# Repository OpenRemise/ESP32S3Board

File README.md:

# ESP32S3Board

<a href="https://openremise.at">
<picture>
  <source media="(prefers-color-scheme: dark)" srcset="https://github.com/OpenRemise/.github/raw/master/data/icons/icon_dark.svg">
  
</picture>
</a>

The EPS32S3Board was a prototype of a board with ESP32-S3 processor in [Arduino](https://www.arduino.cc/) form factor. Due to the inadequacies of the stackable headers, Arduino compatibility was abandoned and single-board solutions are now used.

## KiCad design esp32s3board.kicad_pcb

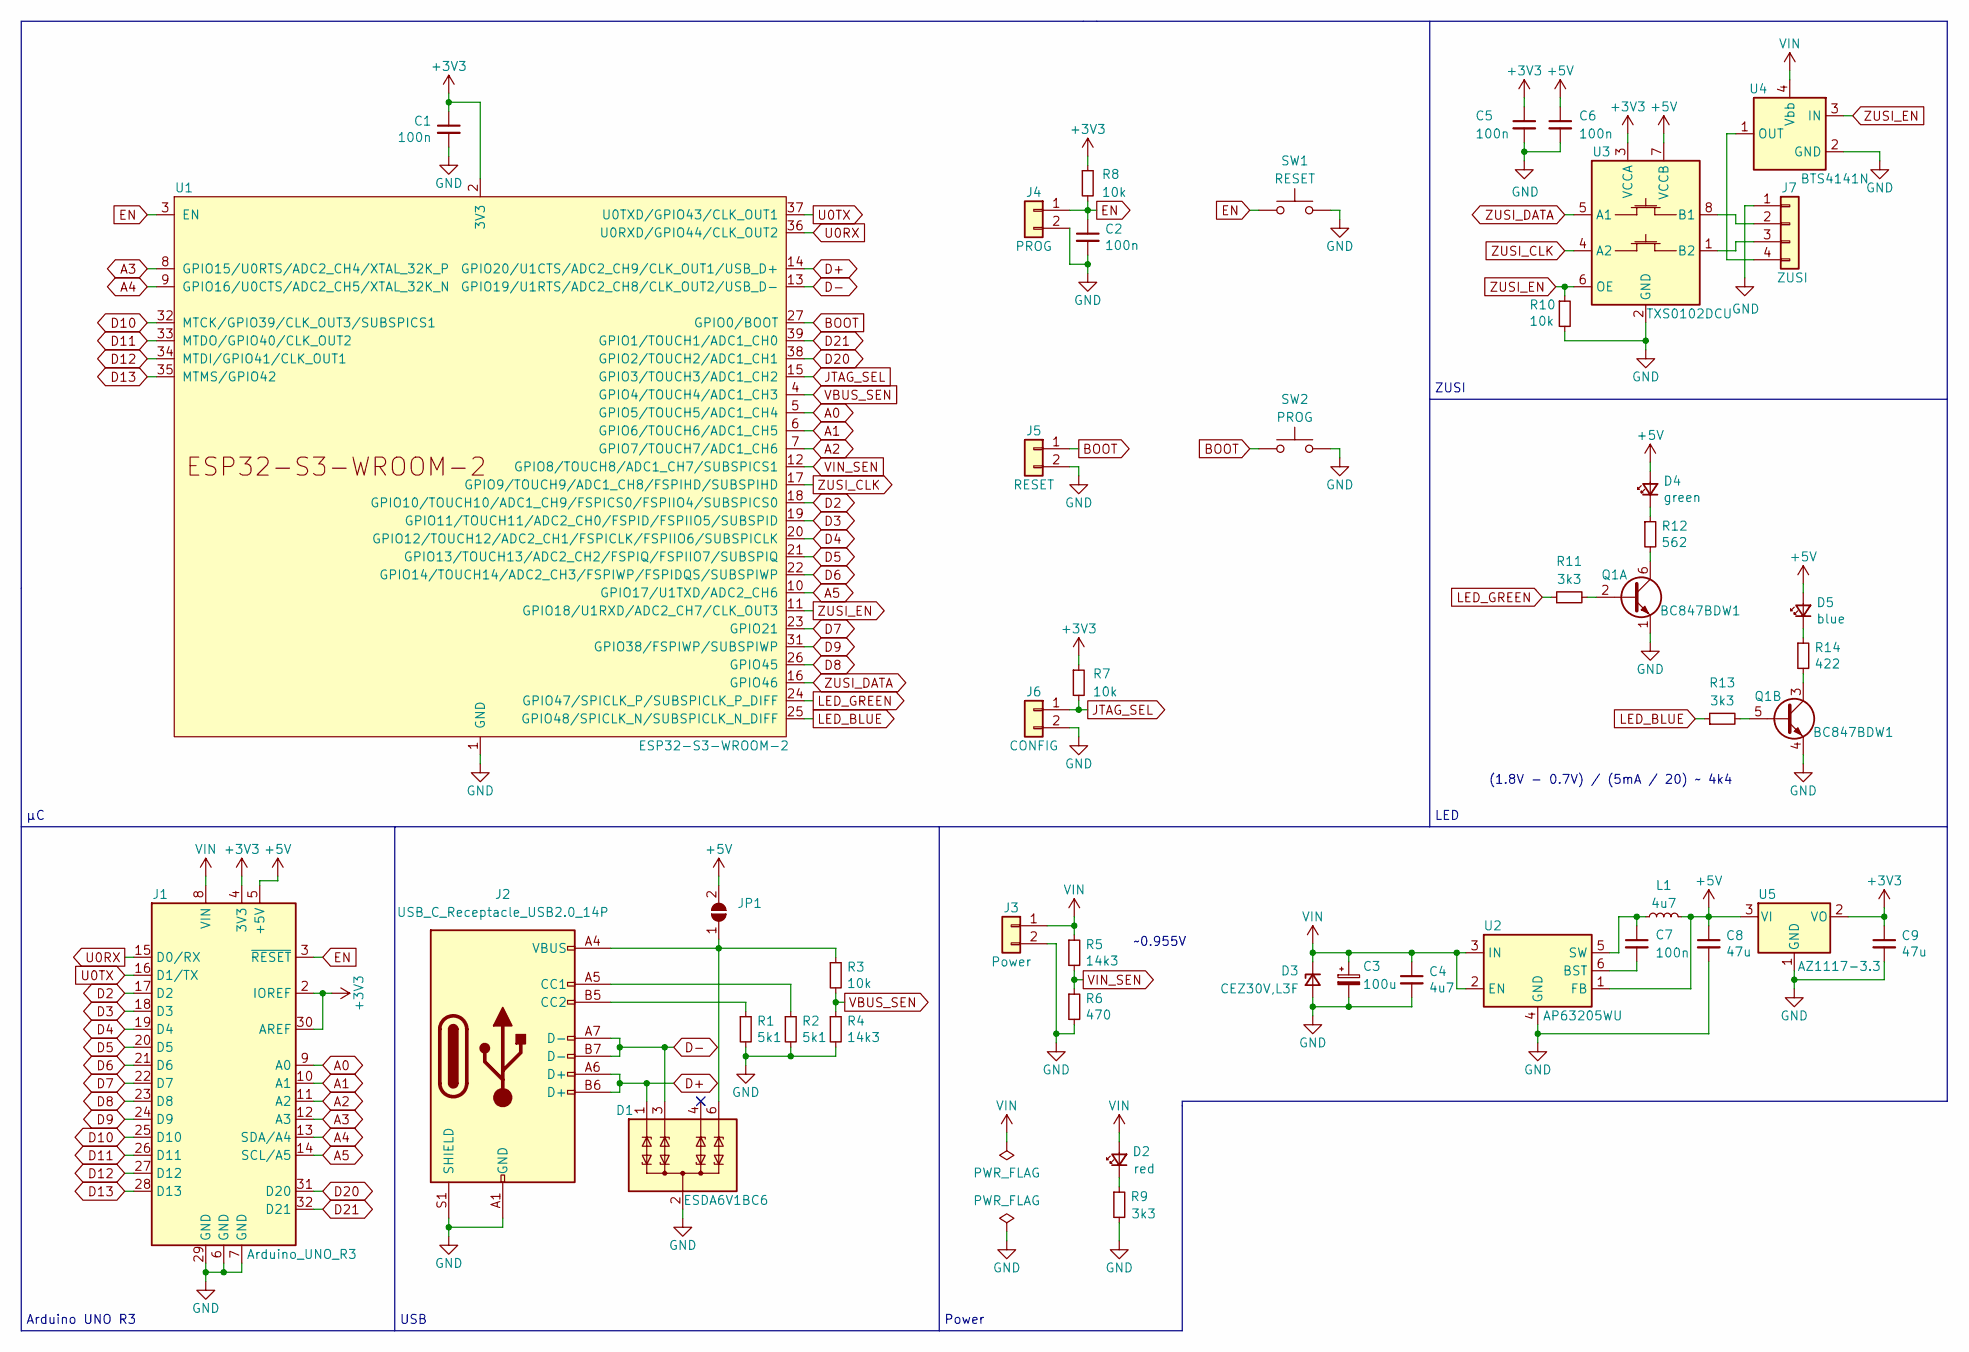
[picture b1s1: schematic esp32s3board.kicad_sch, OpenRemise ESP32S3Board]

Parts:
C1, C2, C5, C6, C7: 100n; C_0402_1005Metric
C3: 100u; CP_Elec_6.3x7.7
C4: 4u7; C_1206_3216Metric
C8, C9: 47u; C_1206_3216Metric
D1: ESDA6V1BC6; SOT-23-6
D2: red; D_0402_1005Metric
D3: CEZ30V,L3F; D_SOD-523
D4: green; D_0402_1005Metric
D5: blue; D_0402_1005Metric
J1: Arduino_UNO_R3; Arduino_UNO_R3_WithMountingHoles
J2: USB_C_Receptacle_USB2.0_14P; USB_C_Receptacle_GCT_USB4105-xx-A_16P_TopMnt_Horizontal
J3: Power; PinHeader_1x02_P2.54mm_Horizontal
J4: PROG; PinHeader_1x02_P2.54mm_Horizontal
J5: RESET; PinHeader_1x02_P2.54mm_Horizontal
J6: CONFIG; PinHeader_1x02_P2.54mm_Horizontal
J7: ZUSI; JST_SH_SM04B-SRSS-TB_1x04-1MP_P1.00mm_Horizontal
JP1: SolderJumper_2_Open; SolderJumper-2_P1.3mm_Open_Pad1.0x1.5mm
L1: 4u7; L_0805_2012Metric
Q1: BC847BDW1; SOT-363_SC-70-6
R1, R2: 5k1; R_0402_1005Metric
R3, R7, R8, R10: 10k; R_0402_1005Metric
R4, R5: 14k3; R_0402_1005Metric
R6: 470; R_0402_1005Metric
R9, R11, R13: 3k3; R_0402_1005Metric
R12: 562; R_0402_1005Metric
R14: 422; R_0402_1005Metric
SW1: RESET; SW_SPST_EVPBF
SW2: PROG; SW_SPST_EVPBF
U1: ESP32-S3-WROOM-2
U2: AP63205WU; TSOT-23-6
U3: TXS0102DCU; VSSOP-8_2.3x2mm_P0.5mm
U4: BTS4141N; SOT-223
U5: AZ1117-3.3; SOT-89-3

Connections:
+3V3: C1.1, C5.1, C9.1, J1.2 (IOREF), J1.4 (3V3), J1.30 (AREF), R7.1, R8.1, U1.2 (3V3), U3.3 (VCCA), U5.2 (VO)
+5V: C6.1, C8.1, D4.2 (A), D5.2 (A), J1.5 (+5V), JP1.2 (B), L1.2, U2.1 (FB), U3.7 (VCCB), U5.3 (VI)
A0: J1.9 (A0), U1.5 (GPIO5/TOUCH5/ADC1_CH4)
A1: J1.10 (A1), U1.6 (GPIO6/TOUCH6/ADC1_CH5)
A2: J1.11 (A2), U1.7 (GPIO7/TOUCH7/ADC1_CH6)
A3: J1.12 (A3), U1.8 (GPIO15/U0RTS/ADC2_CH4/XTAL_32K_P)
A4: J1.13 (SDA/A4), U1.9 (GPIO16/U0CTS/ADC2_CH5/XTAL_32K_N)
A5: J1.14 (SCL/A5), U1.10 (GPIO17/U1TXD/ADC2_CH6)
BOOT: J5.1, SW2.1, U1.27 (GPIO0/BOOT)
D2: J1.17 (D2), U1.18 (GPIO10/TOUCH10/ADC1_CH9/FSPICS0/FSPIIO4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)
D3: J1.18 (D3), U1.19 (GPIO11/TOUCH11/ADC2_CH0/FSPID/FSPIIO5/S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)
D4: J1.19 (D4), U1.20 (GPIO12/TOUCH12/ADC2_CH1/FSPICLK/FSPIIO6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)
D5: J1.20 (D5), U1.21 (GPIO13/TOUCH13/ADC2_CH2/FSPIQ/FSPIIO7/S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)
D6: J1.21 (D6), U1.22 (GPIO14/TOUCH14/ADC2_CH3/FSPIWP/FSPIDQS/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)
D7: J1.22 (D7), U1.23 (GPIO21)
D8: J1.23 (D8), U1.26 (GPIO45)
D9: J1.24 (D9), U1.31 (GPIO38/FSPIWP/SUBSPIWP)
D10: J1.25 (D10), U1.32 (MTCK/GPIO39/CLK_OUT3/SUBSPICS1)
D11: J1.26 (D11), U1.33 (MTDO/GPIO40/CLK_OUT2)
D12: J1.27 (D12), U1.34 (MTDI/GPIO41/CLK_OUT1)
D13: J1.28 (D13), U1.35 (MTMS/GPIO42)
D20: J1.31 (D20), U1.38 (GPIO2/TOUCH2/ADC1_CH1)
D21: J1.32 (D21), U1.39 (GPIO1/TOUCH1/ADC1_CH0)
D+: D1.1 (TVS1), J2.A6 (D+), J2.B6 (D+), U1.14 (GPIO20/U1CTS/ADC2_CH9/CLK_OUT1/USB_D+)
D-: D1.3 (TVS2), J2.A7 (D-), J2.B7 (D-), U1.13 (GPIO19/U1RTS/ADC2_CH8/CLK_OUT2/USB_D-)
EN: C2.1, J1.3 (~RESET), J4.1, R8.2, SW1.1, U1.3 (EN)
GND: C1.2, C2.2, C3.2, C4.2, C5.2, C6.2, C8.2, C9.2, D1.2 (COM), D1.5 (COM), D3.2 (A), J1.6 (GND), J1.7 (GND), J1.29 (GND), J2.A1 (GND), J2.A12 (GND), J2.B1 (GND), J2.B12 (GND), J2.S1 (SHIELD), J3.2, J4.2, J5.2, J6.2, J7.1, Q1.1 (E1), Q1.4 (E2), R1.2, R2.2, R4.2, R6.2, R9.2, R10.2, SW1.2, SW2.2, U1.1 (GND), U1.40 (GND), U1.41 (GND), U2.4 (GND), U3.2 (GND), U4.2 (GND), U5.1 (GND)
JTAG_SEL: J6.1, R7.2, U1.15 (GPIO3/TOUCH3/ADC1_CH2)
LED_BLUE: R13.1, U1.25 (GPIO48/SPICLK_N/SUBSPICLK_N_DIFF)
LED_GREEN: R11.1, U1.24 (GPIO47/SPICLK_P/SUBSPICLK_P_DIFF)
unnamed: D1.6 (TVS4), J2.A4 (VBUS), J2.A9 (VBUS), J2.B4 (VBUS), J2.B9 (VBUS), JP1.1 (A), R3.1
unnamed: D2.1 (K), R9.1
unnamed: D4.1 (K), R12.1
unnamed: D5.1 (K), R14.1
unnamed: J2.A5 (CC1), R2.1
unnamed: J2.B5 (CC2), R1.1
unnamed: J7.2, U3.8 (B1)
unnamed: J7.3, U3.1 (B2)
unnamed: J7.4, U4.1 (OUT)
unnamed: Q1.2 (B1), R11.2
unnamed: Q1.6 (C1), R12.2
unnamed: Q1.5 (B2), R13.2
unnamed: Q1.3 (C2), R14.2
unnamed: C7.2, U2.6 (BST)
unnamed: C7.1, L1.1, U2.5 (SW)
U0RX: J1.15 (D0/RX), U1.36 (U0RXD/GPIO44/CLK_OUT2)
U0TX: J1.16 (D1/TX), U1.37 (U0TXD/GPIO43/CLK_OUT1)
VBUS_SEN: R3.2, R4.1, U1.4 (GPIO4/TOUCH4/ADC1_CH3)
VIN: C3.1, C4.1, D2.2 (A), D3.1 (K), J1.8 (VIN), J3.1, R5.1, U2.2 (EN), U2.3 (IN), U4.4 (Vbb)
VIN_SEN: R5.2, R6.1, U1.12 (GPIO8/TOUCH8/ADC1_CH7/SUBSPICS1)
ZUSI_CLK: U1.17 (GPIO9/TOUCH9/ADC1_CH8/FSPIHD/SUBSPIHD), U3.4 (A2)
ZUSI_DATA: U1.16 (GPIO46), U3.5 (A1)
ZUSI_EN: R10.1, U1.11 (GPIO18/U1RXD/ADC2_CH7/CLK_OUT3), U3.6 (OE), U4.3 (IN)

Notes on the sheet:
(1.8V - 0.7V) / (5mA / 20) ~ 4k4
USB
ZUSI
~0.955V
Arduino UNO R3
LED
Power

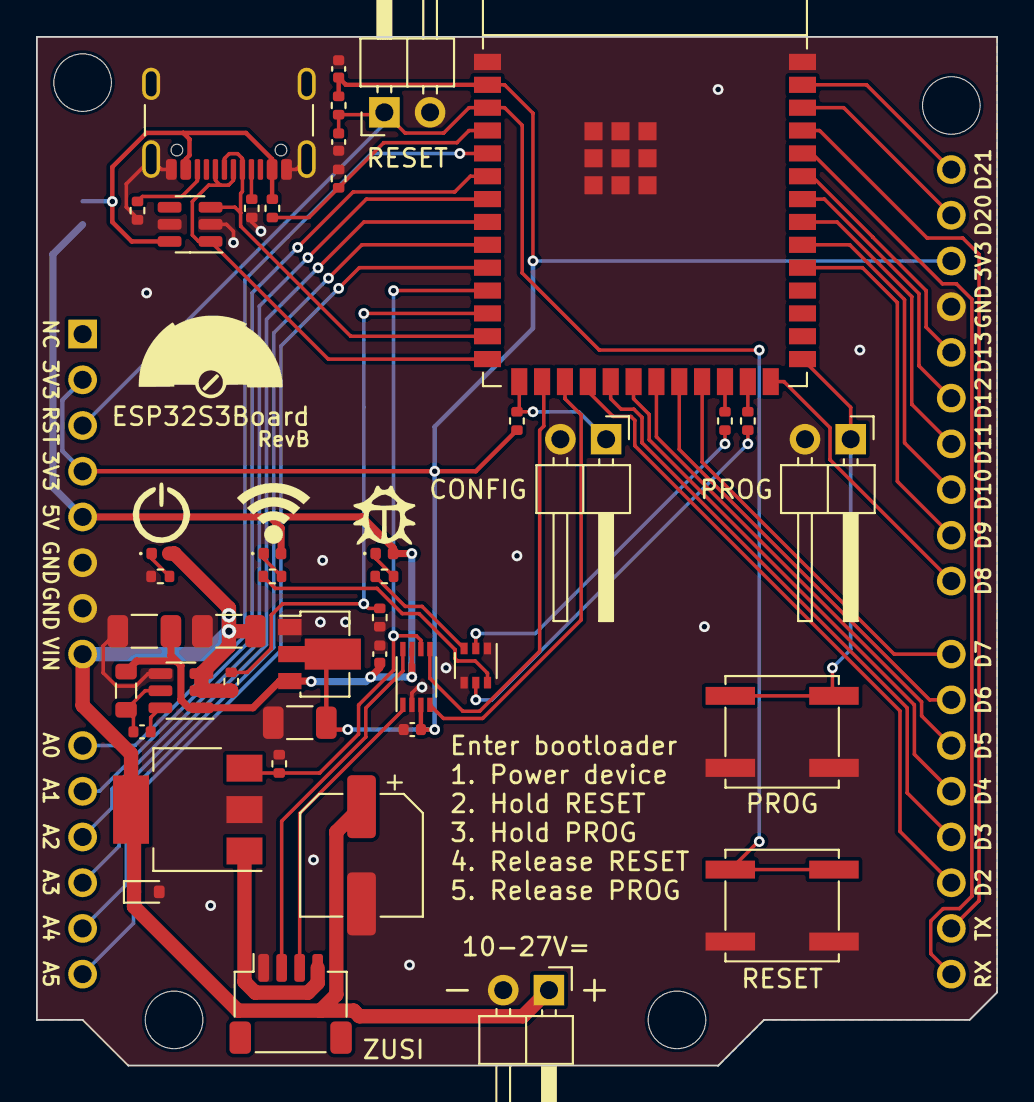
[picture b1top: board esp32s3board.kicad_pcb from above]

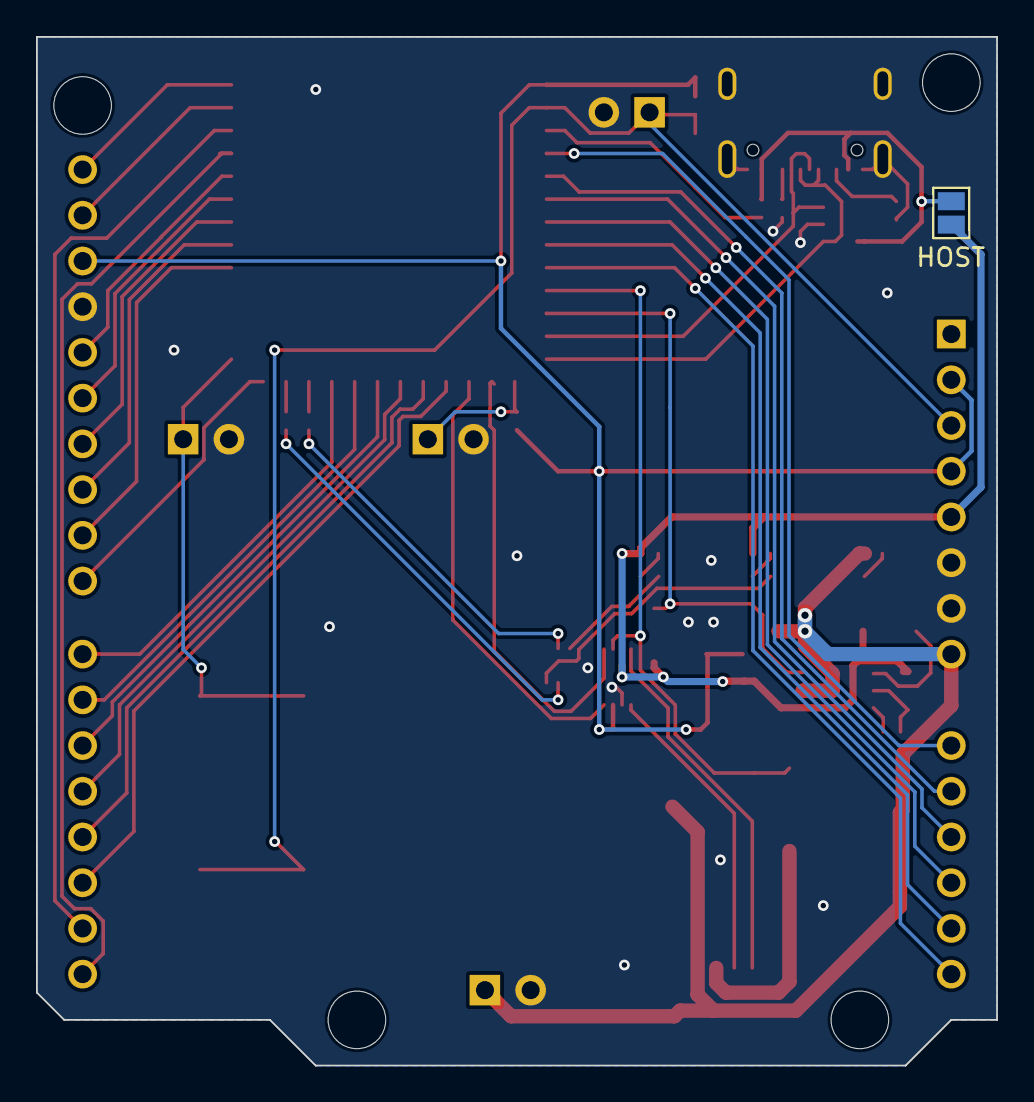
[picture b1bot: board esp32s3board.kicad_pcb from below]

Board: 2 copper layers, 53.3 x 57.2 mm, 45 parts (2 on the bottom side), 53 nets.

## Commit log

2024-01-19 Switch to SMD USB plug
2024-01-19 Switch to horizontal pin headers
2024-08-15 chore: migrate to KiCad 8.0
2024-11-01 feat: revision A
2024-11-19 feat: archive
